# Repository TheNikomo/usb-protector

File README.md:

# USB Protector

Simple board I made to get used to KiCad

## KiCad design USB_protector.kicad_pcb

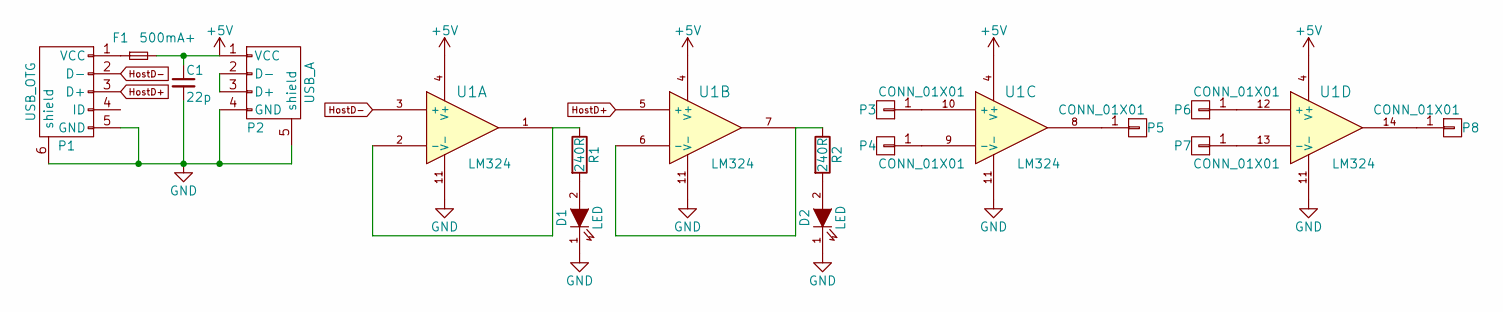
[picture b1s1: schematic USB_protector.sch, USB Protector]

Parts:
C1: 22p; C_0805_HandSoldering
D1, D2: LED; C_1206_HandSoldering
F1: 500mA+; R_1812_HandSoldering
P1: USB_OTG; USB_Micro-B-SMD
P2: USB_A
P3, P4, P5, P6, P7, P8: CONN_01X01; Pin_Header_Straight_1x01
R1, R2: 240R; R_0603_HandSoldering
U1: LM324; SOIC-14_3.9x8.7mm_Pitch1.27mm

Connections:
+5V: C1.1, F1.2, P2.1 (VCC), U1.4 (V+)
GND: C1.2, D1.1 (K), D2.1 (K), P1.5 (GND), P1.6 (shield), P2.4 (GND), P2.5 (shield), U1.11 (V-)
HostD+: P1.3 (D+), U1.5 (+)
HostD-: P1.2 (D-), U1.3 (+)
unnamed: D1.2 (A), R1.2
unnamed: D2.2 (A), R2.2
unnamed: F1.1, P1.1 (VCC)
unnamed: P2.2 (D-), P2.3 (D+)
unnamed: P3.1, U1.10 (+)
unnamed: P4.1, U1.9 (-)
unnamed: P5.1, U1.8
unnamed: P6.1, U1.12 (+)
unnamed: P7.1, U1.13 (-)
unnamed: P8.1, U1.14
unnamed: R1.1, U1.1, U1.2 (-)
unnamed: R2.1, U1.6 (-), U1.7

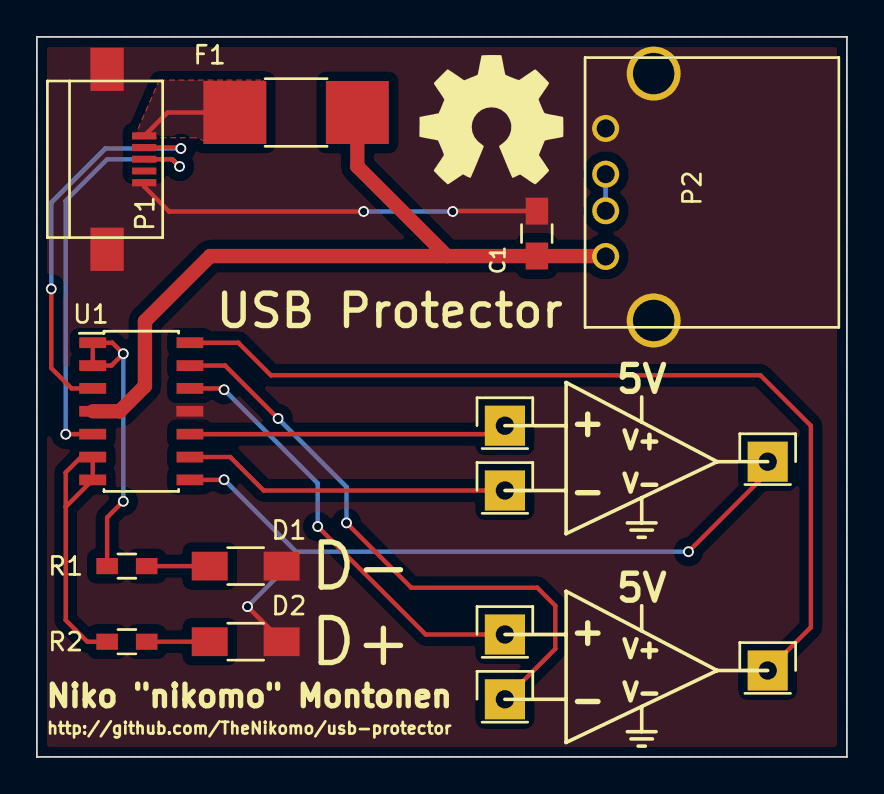
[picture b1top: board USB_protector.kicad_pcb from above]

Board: 2 copper layers, 45.0 x 40.0 mm, 15 parts (0 on the bottom side), 16 nets.

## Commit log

2015-06-22 Initial commit
    Revision 1
    Board created to get used to working with KiCad
2015-06-22 Added license
    Forgot to add license
2015-06-22 Added 3d render
